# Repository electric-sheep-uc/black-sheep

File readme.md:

# Electric Sheep Humanoid Robot Platform V1

This repository contains a snapshot of the
[Electric Sheep](https://humanoid.science) humanoid robotics platform as
presented in the 2019 RoboCup competition in Sydney, Australia. Please observe
the [license](LICENSE) in this repository (projects used in this release have
their own licenses either within their directories or in their source files).

We recommend that you read the technical report [here](docs/paper.pdf).

## Details

The following is intended to make understanding and using the platform easier.

**NOTE:** Vision processing will be added at a later date.

### Electronics

* [Design](docs/design-pcb.md) - Circuit design and BOM.

### Hardware

* [Design](docs/design-hw.md) - Hardware design and BOM.
* [Assembly](docs/assembly-hw.md) - Assembly of the platform.

### Source

* [Compiling](docs/compiling.md) - Compiling the `source` code.
* [Running](docs/running.md) - Running the code.

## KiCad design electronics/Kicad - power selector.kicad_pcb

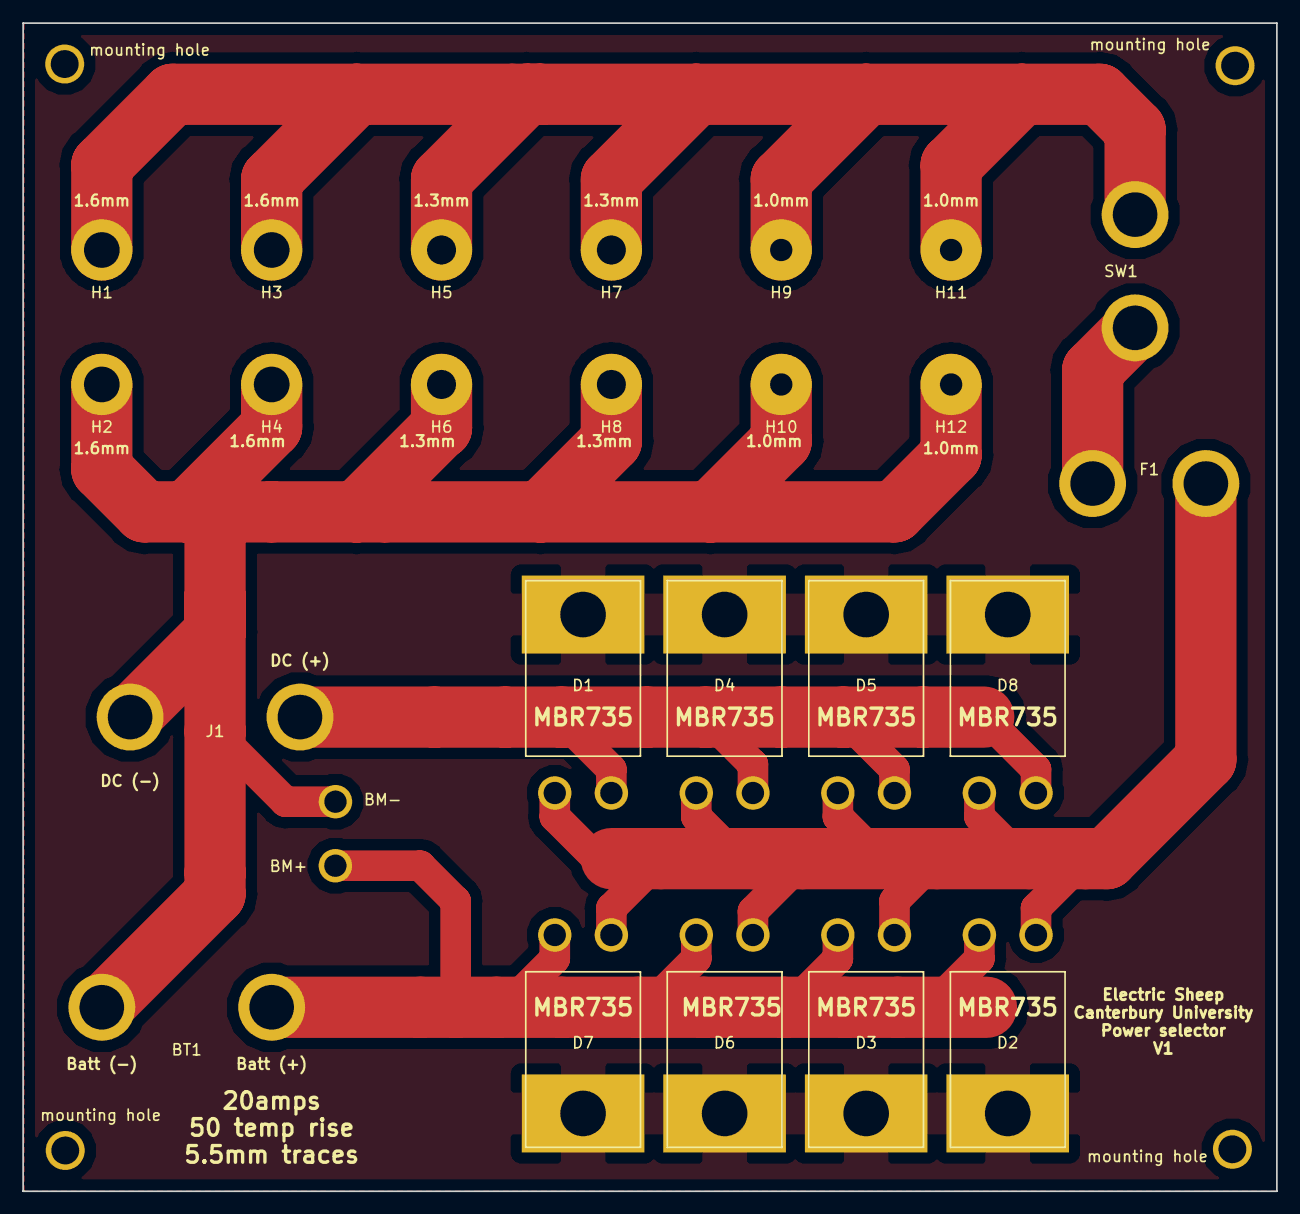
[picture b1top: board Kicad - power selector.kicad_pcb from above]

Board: 2 copper layers, 112.5 x 104.8 mm, 24 parts (0 on the bottom side), 2 nets.

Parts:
BT1: Battery
D1, D2, D3, D4, D5, D6, D7, D8: MBR735
F1: Fuse
H1, H2, H3, H4: MountingHole_Pad; 1.6mm hole
H5, H6, H7, H8: MountingHole_Pad; 1.3mm
H9, H10, H11, H12: MountingHole_Pad; 1.0mm
J1: Conn_Coaxial_Power; Power
SW1: SW_DIP_x01; Switch

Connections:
unnamed: D1.4, D2.4, D3.4, D4.4, D5.4, D6.4, D7.4, D8.4
unnamed: BT1.+, BT1.-, D1.1, D1.3, D2.1, D2.3, D3.1, D3.3, D4.1, D4.3, D5.1, D5.3, D6.1, D6.3, D7.1, D7.3, D8.1, D8.3, F1.1, F1.2, H1.1, H2.1, H3.1, H4.1, H5.1, H6.1, H7.1, H8.1, H9.1, H10.1, H11.1, H12.1, J1.1, J1.2, SW1.1, SW1.2

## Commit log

2019-07-08 Document compiling process
2019-07-08 Add hardware source files
2019-07-08 Headless build script for project
2019-07-08 Build script readme
2019-07-08 Basic information on running code
2019-07-08 Add stripped source
2019-07-08 Add license to the release
2019-07-08 Basic readme
2019-07-08 Ignore Vim swap files
2019-07-08 Add power PBC to release
2019-07-08 Power PCB documentation
2019-07-08 Add diodes to component list
2019-07-08 Correct spelling mistake
2019-07-08 Note about vision processing
2019-07-08 Simple discussion about hardware design
2019-07-14 Mention the licenses of other repositories
2019-07-14 Stand-in for assembly instructions
2019-07-14 BOM and discussion
2019-07-14 Add initial version of technical report paper
2019-07-25 Update release paper
2019-07-25 Links need to go up to parent directory first
